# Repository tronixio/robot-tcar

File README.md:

# DRAFT - ROBOT - TCAR 4 Wheels.

## TCAR Features.

- 4 Wheels.
- 4 DC Motors.
- Power 2xCells 18650 Lithium Ion Rechargeable Batteries, with embedded charger.
- [4WD Motor Smart Car Chassis.](http://www.dagurobot.com/Robot-Chassis/HC021-P)

## TCAR All Schematics.

- [TODO - MCU Board PIC-16BIT.](https://github.com/tronixio/robot-tcar/blob/main/Kicad/mcu/extras/schematic.pdf)
- [DRAFT - Motors Board LP298.](https://github.com/tronixio/robot-tcar/blob/main/Kicad/motors/extras/schematic.pdf)

<!--
## TCAR Code.

- [PWM.](https://github.com/tronixio/robot-tbot/blob/main/Code/pwm/)

## TCAR MCU PIC 16Bit Top.

## TCAR MCU PIC 16Bit Bottom.

-->

## TCAR Motor Top.

## TCAR Motor Bottom.

!!! note

    - TODO : Work in progress, prototype was not good, hardware, PCB and code can be rework.
    - DRAFT : Prototype OK, last check schematic, PCB & code can be modify.

!!! example "DISCLAIMER"

    THIS CODE IS PROVIDED WITHOUT ANY WARRANTY OR GUARANTEES.
    USERS MAY USE THIS CODE FOR DEVELOPMENT AND EXAMPLE PURPOSES ONLY.
    AUTHORS ARE NOT RESPONSIBLE FOR ANY ERRORS, OMISSIONS, OR DAMAGES THAT COULD
    RESULT FROM USING THIS FIRMWARE IN WHOLE OR IN PART.

---

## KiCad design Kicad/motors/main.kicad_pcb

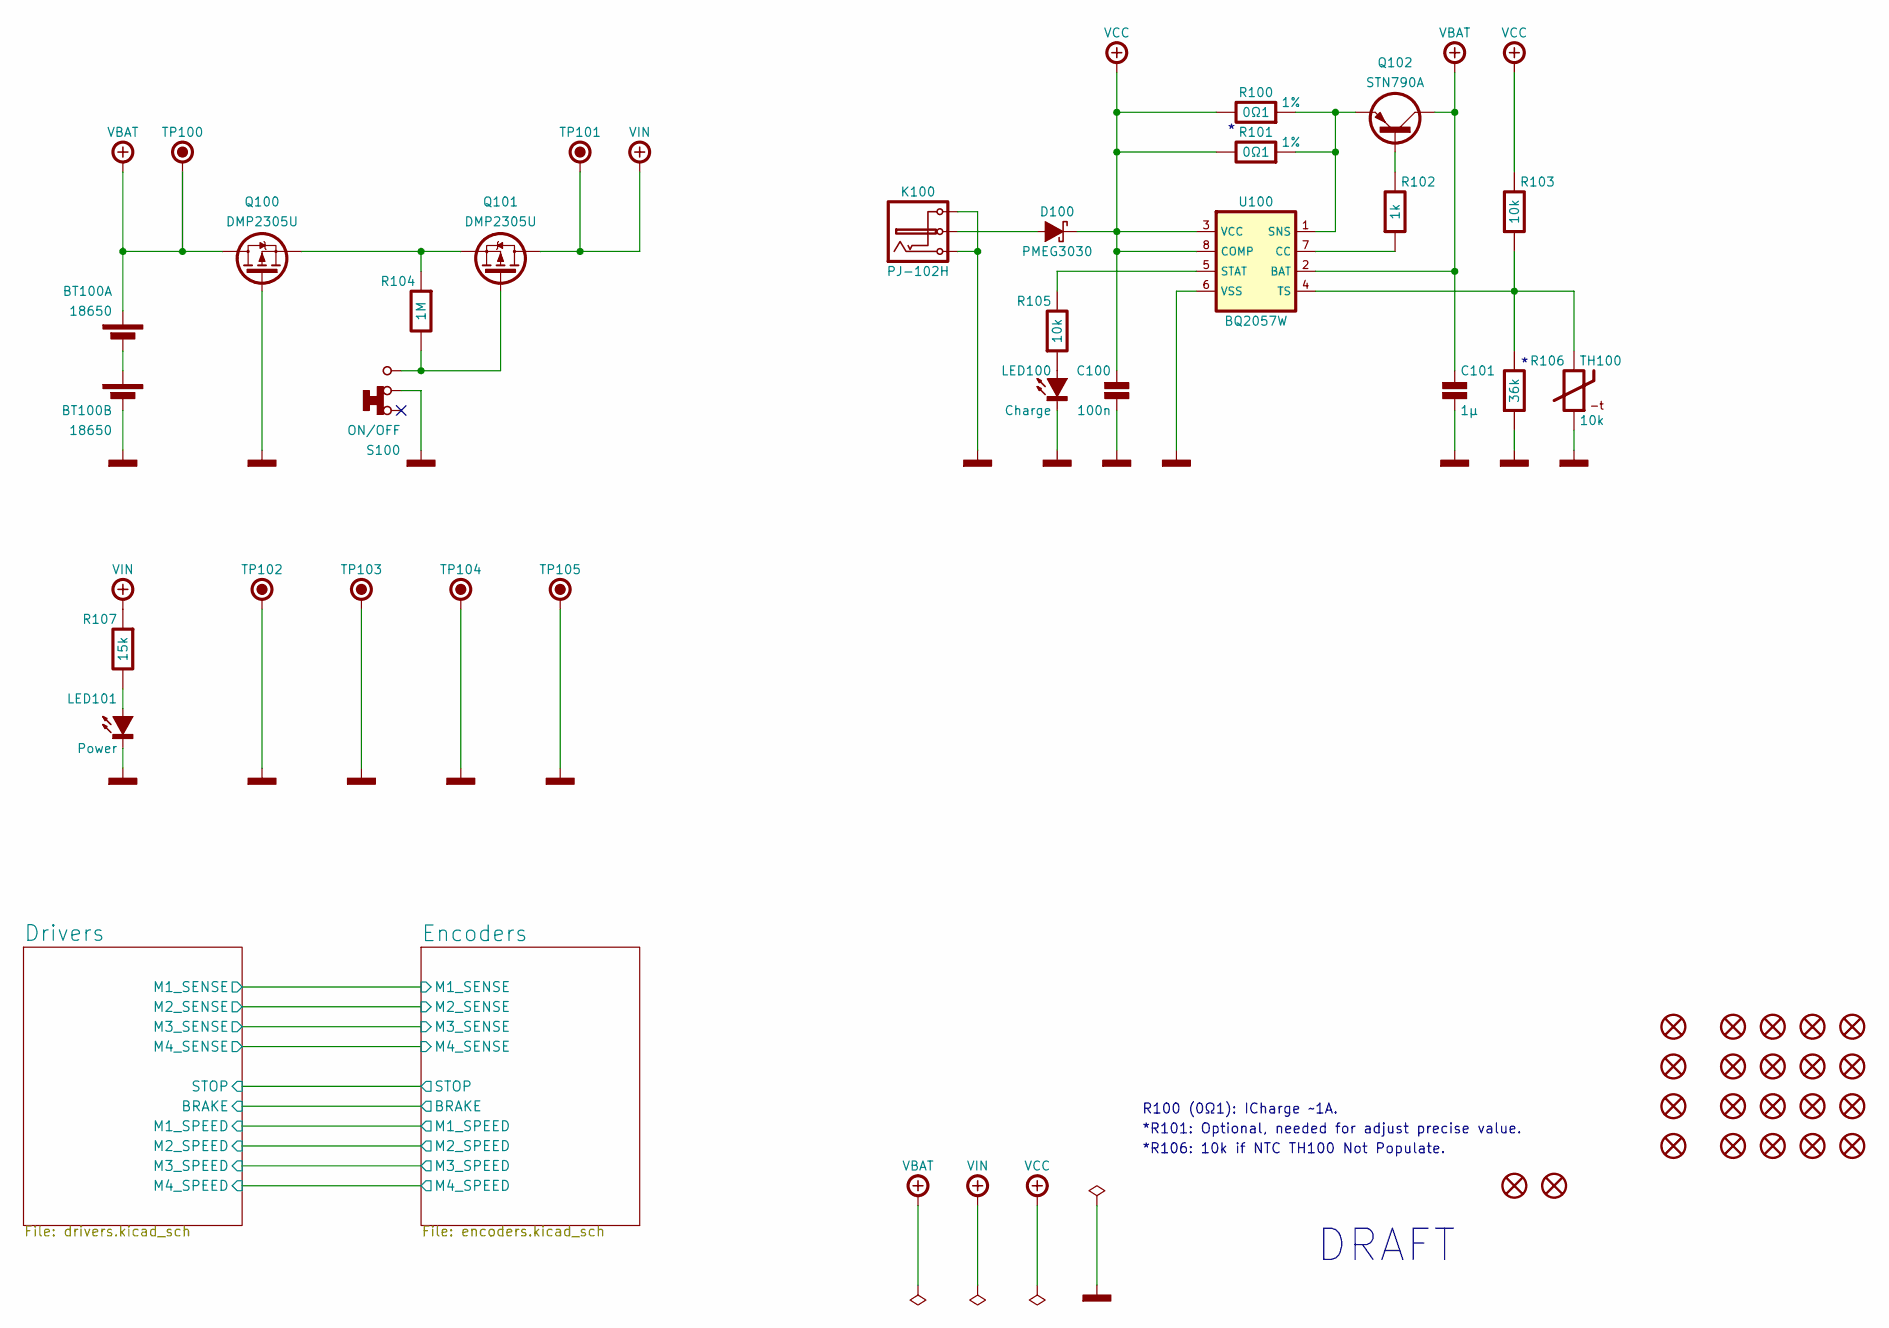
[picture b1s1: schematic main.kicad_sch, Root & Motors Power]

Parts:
BT100: 18650; KEYSTONE-1049; Mouser 534-1049
C100: 100n; CAPACITOR-SMD-1206; Voltage 50V; Tolerance 5%; Mouser 80-C1206C104J5R
C101: 1µ; CAPACITOR-SMD-1206; Voltage 16V; Tolerance 10%; Mouser 80-C1206C105K4R
D100: PMEG3030; SOD-128; Mouser 771-PMEG3030EP115
H101, H102, H103, H104, H105, H106, H107, H108, H109, H110, H111, H112, H113, H114, H115, H116: MOUNTING-HOLE-3MM-MASK
H117, H118, H119, H120: MOUNTING-HOLE-3.5MM
K100: PJ-102H; CUI-PJ-002AH-SMT-TR; Mouser 490-PJ-002AH-SMT-TR
LED100: Charge; LED-SMD-1206; Mouser 604-APT3216LSECKJ3RV
LED101: Power; LED-SMD-1206; Mouser 604-APT3216LSECKJ3RV
Q100, Q101: DMP2305U; SOT-23-3; Mouser 621-DMP2305U-7
Q102: STN790A; SOT-223-3; Mouser 511-STN790A
R100, R101: 0Ω1; RESISTOR-SMD-1210; Tolerance 1%; Mouser 660-SR732ETTER100F
R102: 1k; RESISTOR-SMD-1206; Tolerance 5%; Mouser 660-RK73B2BTTDD102J
R103, R105: 10k; RESISTOR-SMD-1206; Tolerance 5%; Mouser 660-RK73B2BTTDD103J
R104: 1M; RESISTOR-SMD-1206; Tolerance 5%; Mouser 660-RK73B2BTTDD105J
R106: 36k; RESISTOR-SMD-1206; Tolerance 5%; Mouser 660-RK73B2BTTDD363J
R107: 15k; RESISTOR-SMD-1206; Tolerance 5%; Mouser 660-RK73B2BTTDD153J
S100: ON/OFF; E-SWITCH-200USPXT1A1M6RE; Mouser 612-200USP1T1A1M6RE
TH100: 10k; THERMISTOR-SMD; Mouser 594-NTCLE213E3103FL
TP100, TP101, TP102, TP103, TP104, TP105: HARWIN-S1751; Mouser 855-S1751-46
U100: BQ2057W; SOIC-08; Mouser 595-BQ2057WSN
X101, X102: OSHW-5MM

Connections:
+VBAT: BT100.2 (+), C101.1, Q100.3 (D), Q102.2 (C), TP100.1, U100.2 (BAT)
+VCC: C100.1, D100.1 (C), R100.1, R101.1, R103.1, U100.3 (VCC), U100.8 (COMP)
+VIN: Q101.3 (D), R107.2, TP101.1; also elsewhere on the board
GND: BT100.3 (-), C100.2, C101.2, K100.2, K100.3, LED100.1 (C), LED101.1 (C), Q100.1 (G), R106.2, S100.2, TH100.2, TP102.1, TP103.1, TP104.1, TP105.1, U100.6 (VSS); also elsewhere on the board
unnamed: BT100.1 (-), BT100.4 (+)
unnamed: D100.2 (A), K100.1
unnamed: LED100.2 (A), R105.2
unnamed: LED101.2 (A), R107.1
unnamed: Q100.2 (S), Q101.2 (S), R104.2
unnamed: Q101.1 (G), R104.1, S100.3
unnamed: Q102.1 (B), R102.1
unnamed: Q102.3 (E), R100.2, R101.2, U100.1 (SNS)
unnamed: R102.2, U100.7 (CC)
unnamed: R105.1, U100.5 (STAT)
unnamed: R103.2, R106.1, TH100.1, U100.4 (TS)

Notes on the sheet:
DRAFT
*R101: Optional, needed for adjust precise value.
*R106: 10k if NTC TH100 Not Populate.
R100 (0Ω1): ICharge ~1A.

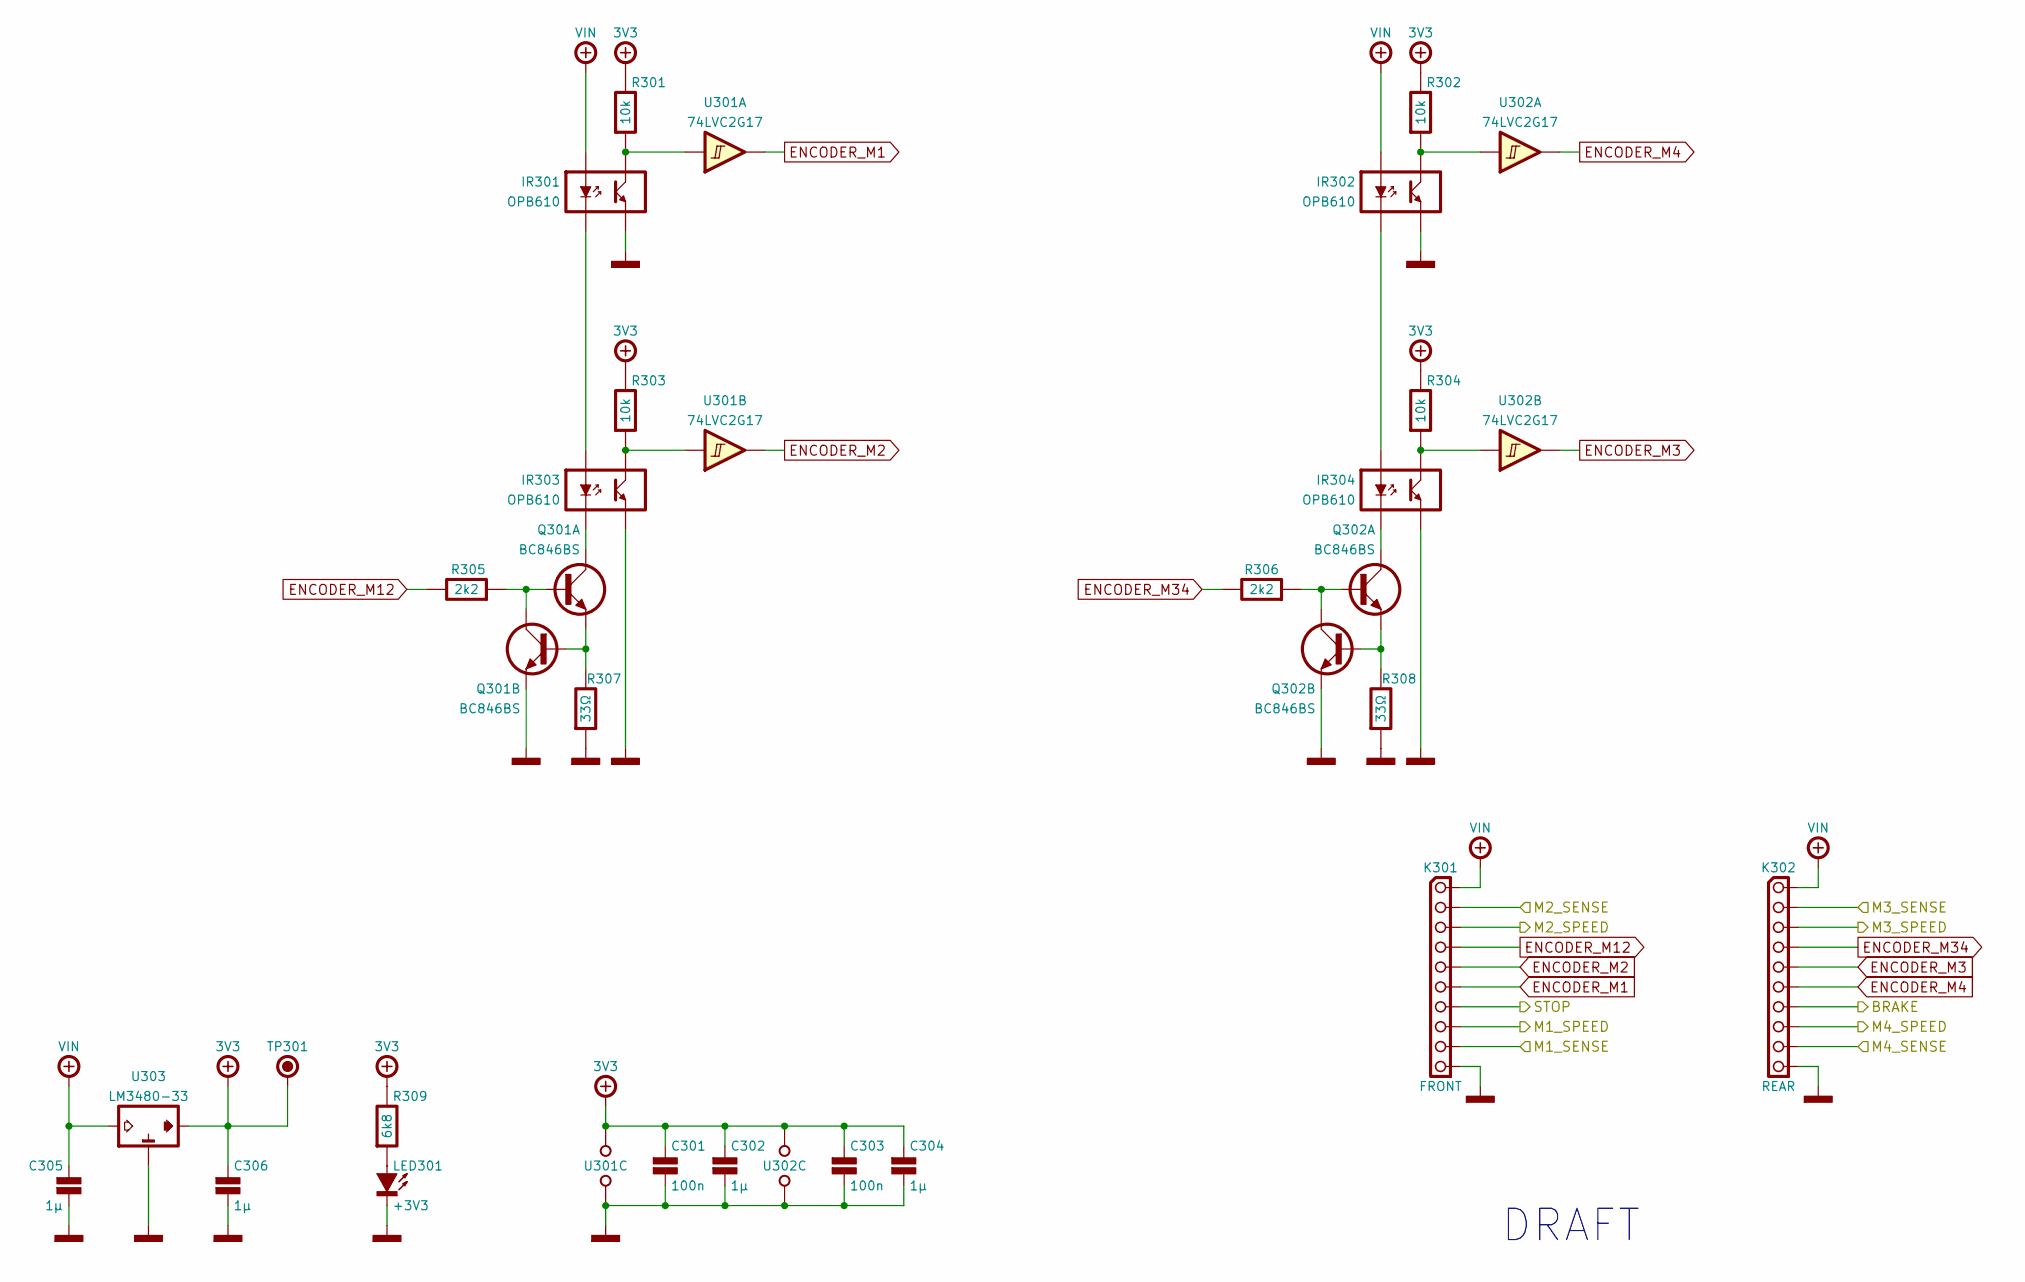
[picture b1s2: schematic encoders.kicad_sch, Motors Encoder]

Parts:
C301, C303: 100n; CAPACITOR-SMD-1206; Voltage 50V; Tolerance 5%; Mouser 80-C1206C104J5R
C302, C304, C305, C306: 1µ; CAPACITOR-SMD-1206; Voltage 16V; Tolerance 10%; Mouser 80-C1206C105K4R
IR301, IR302, IR303, IR304: OPB610; OPB-610; Mouser 828-OPB610
K301: FRONT; HARWIN-M20-782104x; Mouser 855-M20-782104
K302: REAR; HARWIN-M20-782104x; Mouser 855-M20-782104
LED301: +3V3; LED-SMD-1206; Mouser 604-APT3216LSECKJ3RV
Q301, Q302: BC846BS; SC-70-6; Mouser 771-BC846BS115
R301, R302, R303, R304: 10k; RESISTOR-SMD-1206; Tolerance 5%; Mouser 660-RK73B2BTTDD103J
R305, R306: 2k2; RESISTOR-SMD-1206; Tolerance 5%; Mouser 660-RK73B2BTTDD222J
R307, R308: 33Ω; RESISTOR-SMD-1206; Tolerance 5%; Mouser 660-RK73B2BTTDD330J
R309: 6k8; RESISTOR-SMD-1206; Tolerance 5%; Mouser 660-RK73B2BTTD682J
TP301: HARWIN-S1751; Mouser 855-S1751-46
U301, U302: 74LVC2G17; SOT-23-6; Mouser 595-SN74LVC2G17D
U303: LM3480-33; SOT-23-3; Mouser 926-LM3480IM33.3NOPB

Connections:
+3V3: C301.1, C302.1, C303.1, C304.1, C306.1, R301.1, R302.1, R303.1, R304.1, R309.1, TP301.1, U301.5 (VCC), U302.5 (VCC), U303.1 (VOUT); also elsewhere on the board
+VIN: C305.1, IR301.1 (ANODE), IR302.1 (ANODE), K301.1, K302.1, U303.2 (VIN); also elsewhere on the board
/Drivers/BRAKE: K302.7; also elsewhere on the board
/Drivers/M1_SENSE: K301.9; also elsewhere on the board
/Drivers/M1_SPEED: K301.8; also elsewhere on the board
/Drivers/M2_SENSE: K301.2; also elsewhere on the board
/Drivers/M2_SPEED: K301.3; also elsewhere on the board
/Drivers/M3_SENSE: K302.2; also elsewhere on the board
/Drivers/M3_SPEED: K302.3; also elsewhere on the board
/Drivers/M4_SENSE: K302.9; also elsewhere on the board
/Drivers/M4_SPEED: K302.8; also elsewhere on the board
/Drivers/STOP: K301.7; also elsewhere on the board
ENCODER_M1: K301.6, U301.6 (1Y)
ENCODER_M2: K301.5, U301.4 (2Y)
ENCODER_M3: K302.5, U302.4 (2Y)
ENCODER_M4: K302.6, U302.6 (1Y)
ENCODER_M12: K301.4, R305.1
ENCODER_M34: K302.4, R306.1
GND: C301.2, C302.2, C303.2, C304.2, C305.2, C306.2, IR301.4 (EMITTER), IR302.4 (EMITTER), IR303.4 (EMITTER), IR304.4 (EMITTER), K301.10, K302.10, LED301.1 (C), Q301.4 (E), Q302.4 (E), R307.2, R308.2, U301.2 (GND), U302.2 (GND), U303.3 (GND); also elsewhere on the board
unnamed: IR301.2 (CATHODE), IR303.1 (ANODE)
unnamed: IR301.3 (COLLECTOR), R301.2, U301.1 (1A)
unnamed: IR302.2 (CATHODE), IR304.1 (ANODE)
unnamed: IR302.3 (COLLECTOR), R302.2, U302.1 (1A)
unnamed: IR303.2 (CATHODE), Q301.6 (C)
unnamed: IR303.3 (COLLECTOR), R303.2, U301.3 (2A)
unnamed: IR304.2 (CATHODE), Q302.6 (C)
unnamed: IR304.3 (COLLECTOR), R304.2, U302.3 (2A)
unnamed: LED301.2 (A), R309.2
unnamed: Q301.2 (B), Q301.3 (C), R305.2
unnamed: Q301.1 (E), Q301.5 (B), R307.1
unnamed: Q302.2 (B), Q302.3 (C), R306.2
unnamed: Q302.1 (E), Q302.5 (B), R308.1

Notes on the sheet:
DRAFT

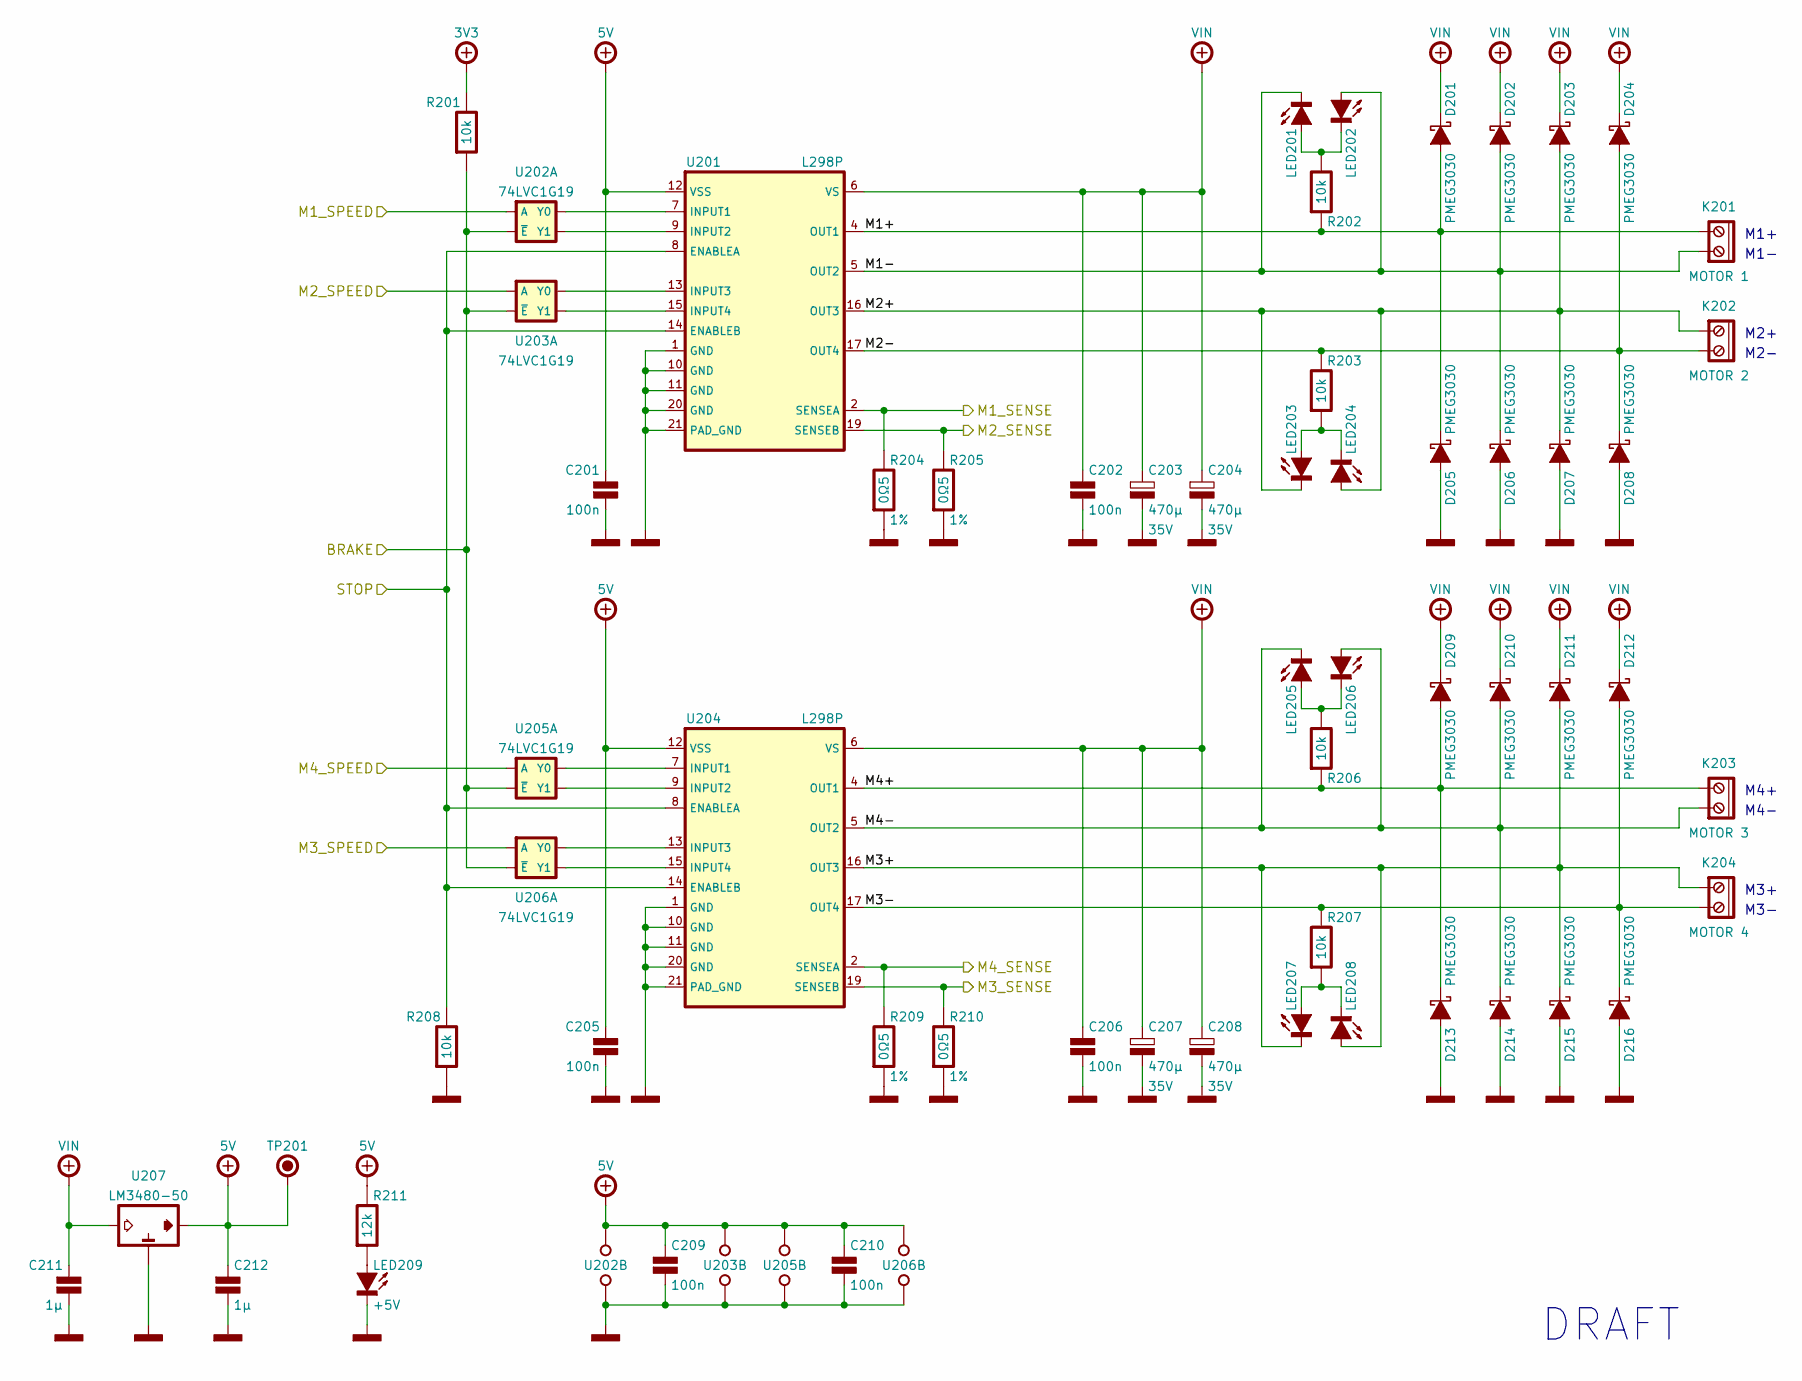
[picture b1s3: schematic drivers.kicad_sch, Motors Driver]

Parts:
C201, C202, C205, C206, C209, C210: 100n; CAPACITOR-SMD-1206; Voltage 50V; Tolerance 5%; Mouser 80-C1206C104J5R
C203, C204, C207, C208: 470µ; CAPACITOR-ELECTROLYTIC-RADIAL-100-160-050-WURTH; Tolerance 20%; Voltage 35V; Mouser 710-860010575013
C211, C212: 1µ; CAPACITOR-SMD-1206; Voltage 16V; Tolerance 10%; Mouser 80-C1206C105K4R
D201, D202, D203, D204, D205, D206, D207, D208, D209, D210, D211, D212, D213, D214, D215, D216: PMEG3030; SOD-128; Mouser 771-PMEG3030EP115
K201: MOTOR 1; CUI-TB006-508-02BE; Mouser 490-TB006-508-02BE
K202: MOTOR 2; CUI-TB006-508-02BE; Mouser 490-TB006-508-02BE
K203: MOTOR 3; CUI-TB006-508-02BE; Mouser 490-TB006-508-02BE
K204: MOTOR 4; CUI-TB006-508-02BE; Mouser 490-TB006-508-02BE
LED201, LED202, LED203, LED204, LED205, LED206, LED207, LED208: RED; LED-SMD-1206; Mouser 604-APT3216LSECKJ3RV
LED209: +5V; LED-SMD-1206; Mouser 604-APT3216LSECKJ3RV
R201, R202, R203, R206, R207, R208: 10k; RESISTOR-SMD-1206; Tolerance 5%; Mouser 660-RK73B2BTTDD103J
R204, R205, R209, R210: 0Ω5; RESISTOR-SMD-1210; Tolerance 1%; Mouser 660-SR732ETTDR499F
R211: 12k; RESISTOR-SMD-1206; Tolerance 5%; Mouser 660-RK73B2BTTD123J
TP201: HARWIN-S1751; Mouser 855-S1751-46
U201, U204: L298P; SOPOWER-20; Mouser 511-L298P-TR
U202, U203, U205, U206: 74LVC1G19; SOT-23-6; Mouser 595-SN74LVC1G19D
U207: LM3480-50; SOT-23-3; Mouser 926-LM3480IM35.0NOPB

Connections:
+3V3: R201.1; also elsewhere on the board
+5V: C201.1, C205.1, C209.1, C210.1, C212.1, R211.1, TP201.1, U201.12 (VSS), U202.5 (VCC), U203.5 (VCC), U204.12 (VSS), U205.5 (VCC), U206.5 (VCC), U207.1 (VOUT)
+VIN: C202.1, C203.1, C204.1, C206.1, C207.1, C208.1, C211.1, D201.1 (C), D202.1 (C), D203.1 (C), D204.1 (C), D209.1 (C), D210.1 (C), D211.1 (C), D212.1 (C), U201.6 (VS), U204.6 (VS), U207.2 (VIN); also elsewhere on the board
/Drivers/BRAKE: R201.2, U202.3 (~E), U203.3 (~E), U205.3 (~E), U206.3 (~E); also elsewhere on the board
/Drivers/M1+: D201.2 (A), D205.1 (C), K201.2, R202.2, U201.4 (OUT1)
/Drivers/M1-: D202.2 (A), D206.1 (C), K201.1, LED201.1 (C), LED202.2 (A), U201.5 (OUT2)
/Drivers/M1_SENSE: R204.1, U201.2 (SENSEA); also elsewhere on the board
/Drivers/M1_SPEED: U202.1 (A); also elsewhere on the board
/Drivers/M2+: D203.2 (A), D207.1 (C), K202.1, LED203.1 (C), LED204.2 (A), U201.16 (OUT3)
/Drivers/M2-: D204.2 (A), D208.1 (C), K202.2, R203.1, U201.17 (OUT4)
/Drivers/M2_SENSE: R205.1, U201.19 (SENSEB); also elsewhere on the board
/Drivers/M2_SPEED: U203.1 (A); also elsewhere on the board
/Drivers/M3+: D211.2 (A), D215.1 (C), K204.1, LED207.1 (C), LED208.2 (A), U204.16 (OUT3)
/Drivers/M3-: D212.2 (A), D216.1 (C), K204.2, R207.1, U204.17 (OUT4)
/Drivers/M3_SENSE: R210.1, U204.19 (SENSEB); also elsewhere on the board
/Drivers/M3_SPEED: U206.1 (A); also elsewhere on the board
/Drivers/M4+: D209.2 (A), D213.1 (C), K203.2, R206.2, U204.4 (OUT1)
/Drivers/M4-: D210.2 (A), D214.1 (C), K203.1, LED205.1 (C), LED206.2 (A), U204.5 (OUT2)
/Drivers/M4_SENSE: R209.1, U204.2 (SENSEA); also elsewhere on the board
/Drivers/M4_SPEED: U205.1 (A); also elsewhere on the board
/Drivers/STOP: R208.1, U201.8 (ENABLEA), U201.14 (ENABLEB), U204.8 (ENABLEA), U204.14 (ENABLEB); also elsewhere on the board
GND: C201.2, C202.2, C203.2, C204.2, C205.2, C206.2, C207.2, C208.2, C209.2, C210.2, C211.2, C212.2, D205.2 (A), D206.2 (A), D207.2 (A), D208.2 (A), D213.2 (A), D214.2 (A), D215.2 (A), D216.2 (A), LED209.1 (C), R204.2, R205.2, R208.2, R209.2, R210.2, U201.1 (GND), U201.10 (GND), U201.11 (GND), U201.20 (GND), U201.21 (PAD_GND), U202.2 (GND), U203.2 (GND), U204.1 (GND), U204.10 (GND), U204.11 (GND), U204.20 (GND), U204.21 (PAD_GND), U205.2 (GND), U206.2 (GND), U207.3 (GND); also elsewhere on the board
unnamed: LED201.2 (A), LED202.1 (C), R202.1
unnamed: LED203.2 (A), LED204.1 (C), R203.2
unnamed: LED205.2 (A), LED206.1 (C), R206.1
unnamed: LED207.2 (A), LED208.1 (C), R207.2
unnamed: LED209.2 (A), R211.2
unnamed: U201.7 (INPUT1), U202.6 (Y0)
unnamed: U201.9 (INPUT2), U202.4 (Y1)
unnamed: U201.13 (INPUT3), U203.6 (Y0)
unnamed: U201.15 (INPUT4), U203.4 (Y1)
unnamed: U204.7 (INPUT1), U205.6 (Y0)
unnamed: U204.9 (INPUT2), U205.4 (Y1)
unnamed: U204.13 (INPUT3), U206.6 (Y0)
unnamed: U204.15 (INPUT4), U206.4 (Y1)

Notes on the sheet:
M3-
M1+
M2+
M4-
M2-
DRAFT
M3+
M4+
M1-

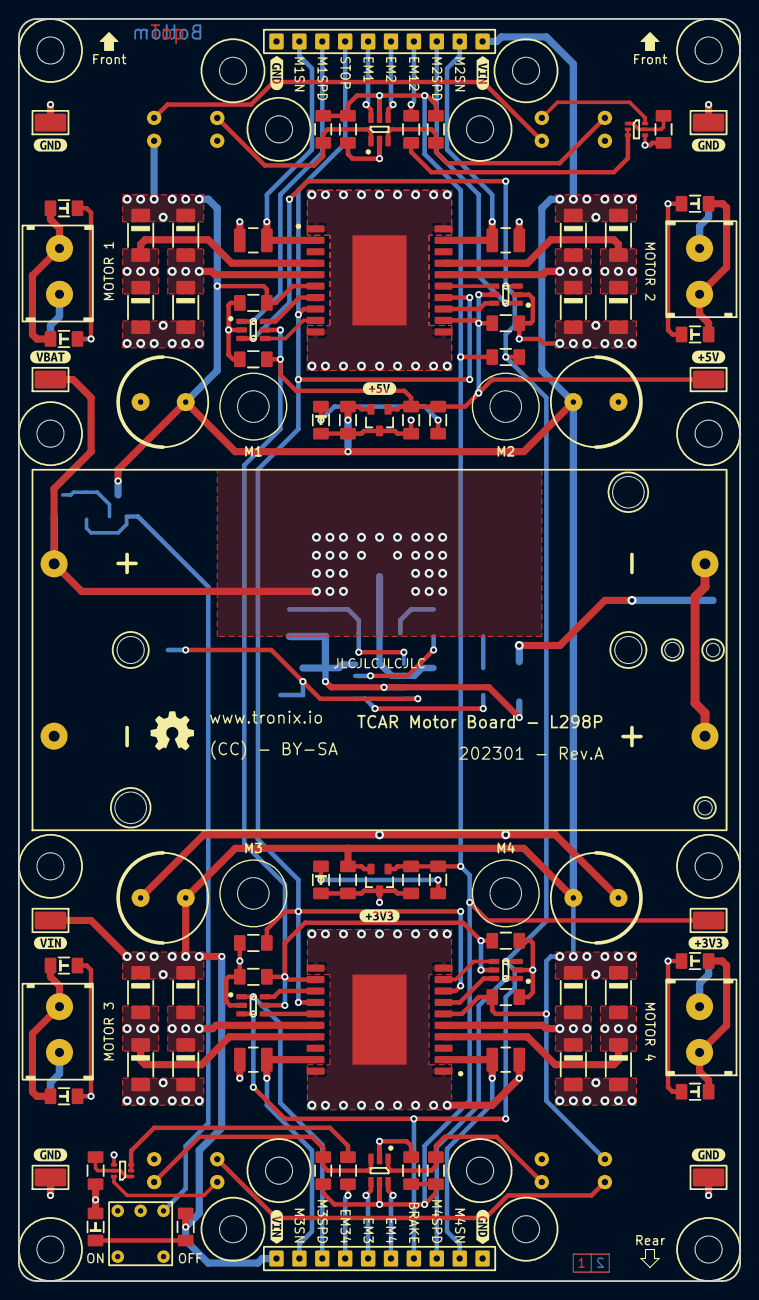
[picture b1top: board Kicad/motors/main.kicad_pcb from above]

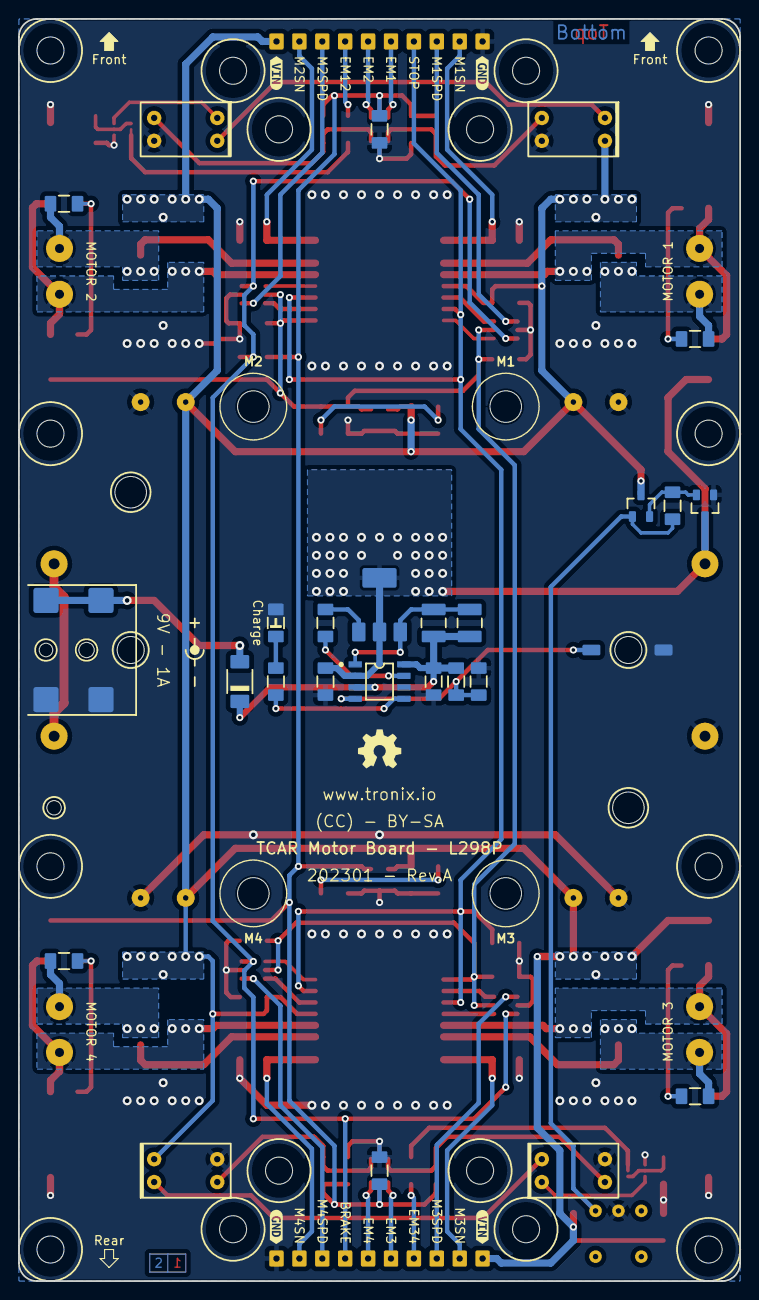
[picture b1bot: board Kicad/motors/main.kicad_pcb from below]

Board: 2 copper layers, 80.0 x 140.0 mm, 155 parts (32 on the bottom side), 67 nets.

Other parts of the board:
kibuzzard-64482FBD: G***; kibuzzard-64482FBD
kibuzzard-64482FE5: G***; kibuzzard-64482FE5
kibuzzard-628974BE, kibuzzard-628974BE#2: G***; kibuzzard-628974BE
kibuzzard-628977DB: G***; kibuzzard-628977DB
kibuzzard-628977F0: G***; kibuzzard-628977F0
kibuzzard-6289753B, kibuzzard-6289753B#2: G***; kibuzzard-6289753B
kibuzzard-6289769F, kibuzzard-6289769F#2: G***; kibuzzard-6289769F
kibuzzard-6289784D: G***; kibuzzard-6289784D
kibuzzard-6289786A: G***; kibuzzard-6289786A
kibuzzard-62897416, kibuzzard-62897416#2: G***; kibuzzard-62897416
kibuzzard-62897505, kibuzzard-62897505#2: G***; kibuzzard-62897505
kibuzzard-62897802: G***; kibuzzard-62897802
kibuzzard-62897881: G***; kibuzzard-62897881

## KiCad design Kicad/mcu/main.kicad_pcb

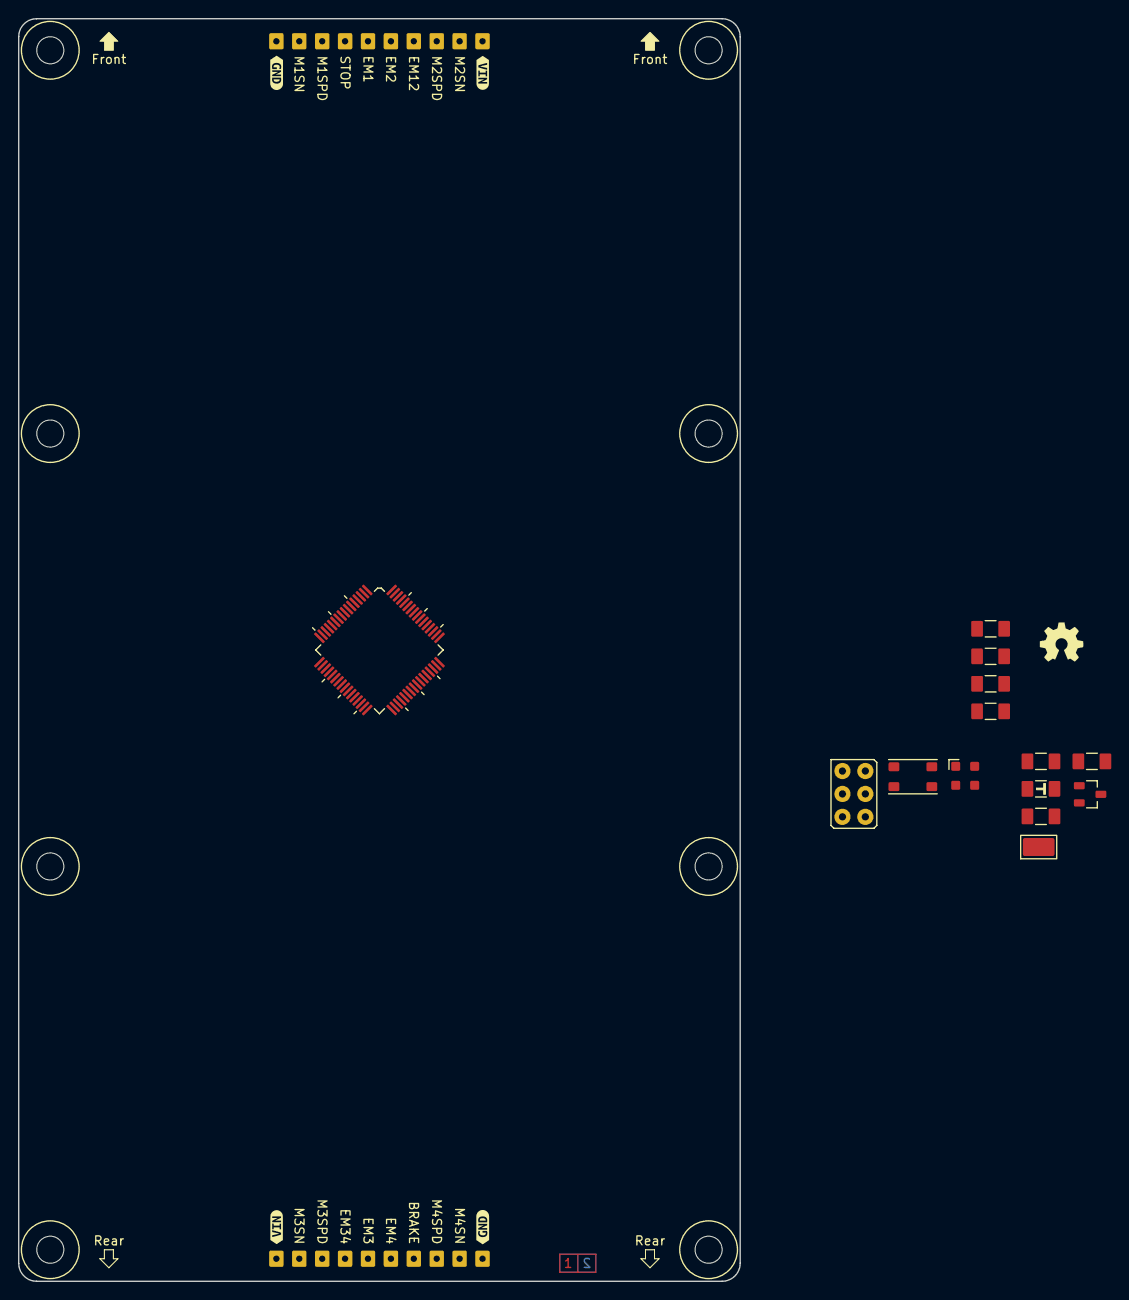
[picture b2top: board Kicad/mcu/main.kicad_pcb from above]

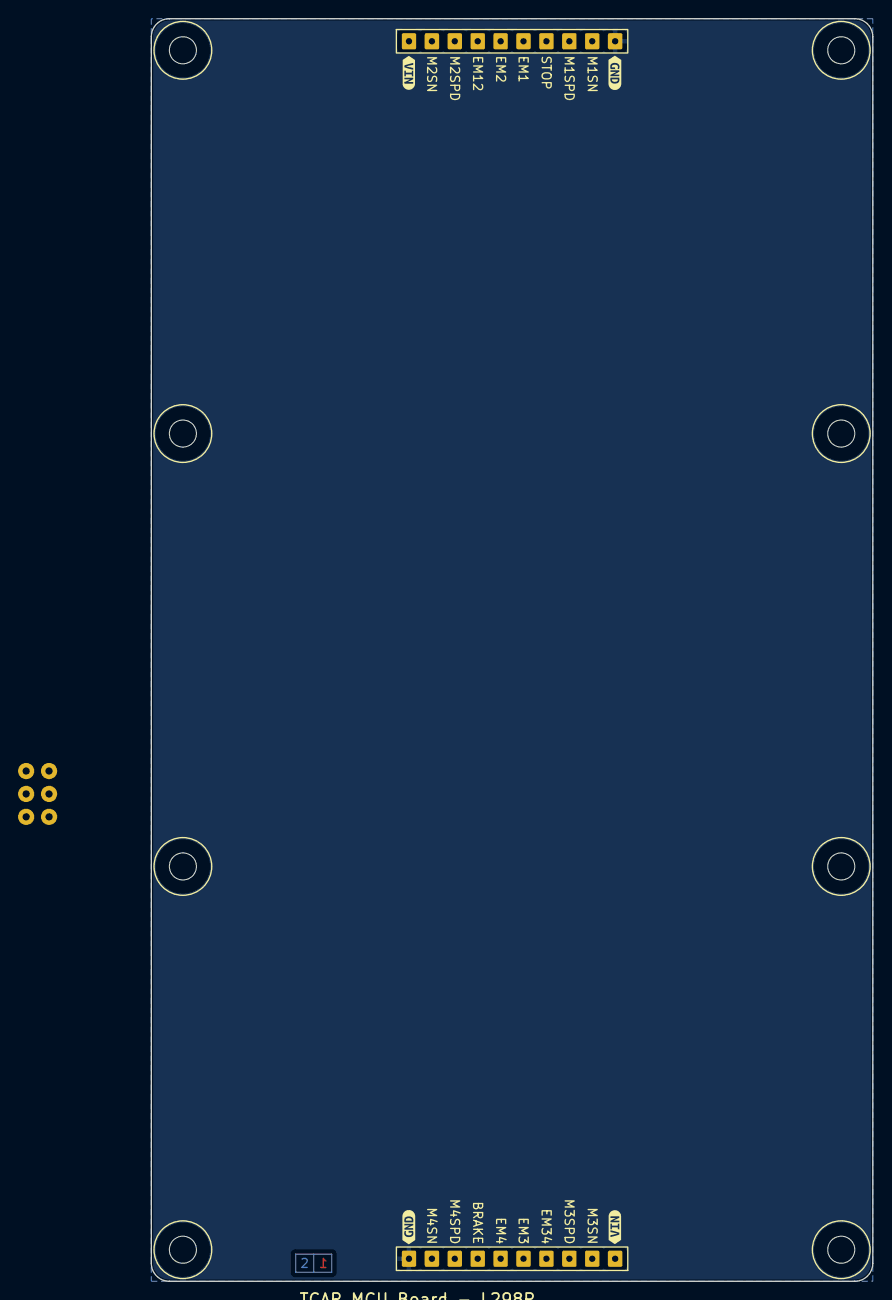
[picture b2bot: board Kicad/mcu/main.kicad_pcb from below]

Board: 2 copper layers, 80.0 x 140.0 mm, 34 parts (7 on the bottom side), 5 nets, no tracks yet.

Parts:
C101, C102: 1µ; CAPACITOR-SMD-1206
C201, C202: 100n; CAPACITOR-SMD-1206
H101, H102, H103, H104, H105, H106, H107, H108: MOUNTING-HOLE-MASK-3MM; MOUNTING-HOLE-3MM-MASK
IC101: LM3480-33; SOT-23-3
IC201: MICROCHIP-PIC24FJ64GA106-TQFP; TQFP-64
K201: ICSP; HARWIN-M20-998034x
K301: Front; HARWIN-M20-782104x
K302: Rear; HARWIN-M20-782104x
LED101: Power; LED-SMD-1206
MEMS201: MICROCHIP-DSC1001C-245760-CDFN; CDFN-3225
R101: 6K8; RESISTOR-SMD-1206
R201: 10K; RESISTOR-SMD-1206
R202: 1K; RESISTOR-SMD-1206
S201: Reset; ALPS-SKRPAC
TP101: HARWIN-S1751
X101, X102: SYMBOL-MISC; OSHW-5MM
kibuzzard-64205CDF, kibuzzard-64205CDF#2, kibuzzard-64205CDF#3, kibuzzard-64205CDF#4: G***; kibuzzard-64205CDF
kibuzzard-628974BE, kibuzzard-628974BE#2, kibuzzard-628974BE#3, kibuzzard-628974BE#4: G***; kibuzzard-628974BE

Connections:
+3V3: C102.1, C202.1, K201.2 (VDD), R101.1, TP101.1
GND: C101.2, C102.2, C201.2, C202.2, IC101.3 (GND), K301.1, K302.1, LED101.1 (C), S201.1, S201.2
unnamed: C201.1, R201.1, R202.2, S201.3, S201.4
unnamed: LED101.2 (A), R101.2
VIN: C101.1, K301.10, K302.10

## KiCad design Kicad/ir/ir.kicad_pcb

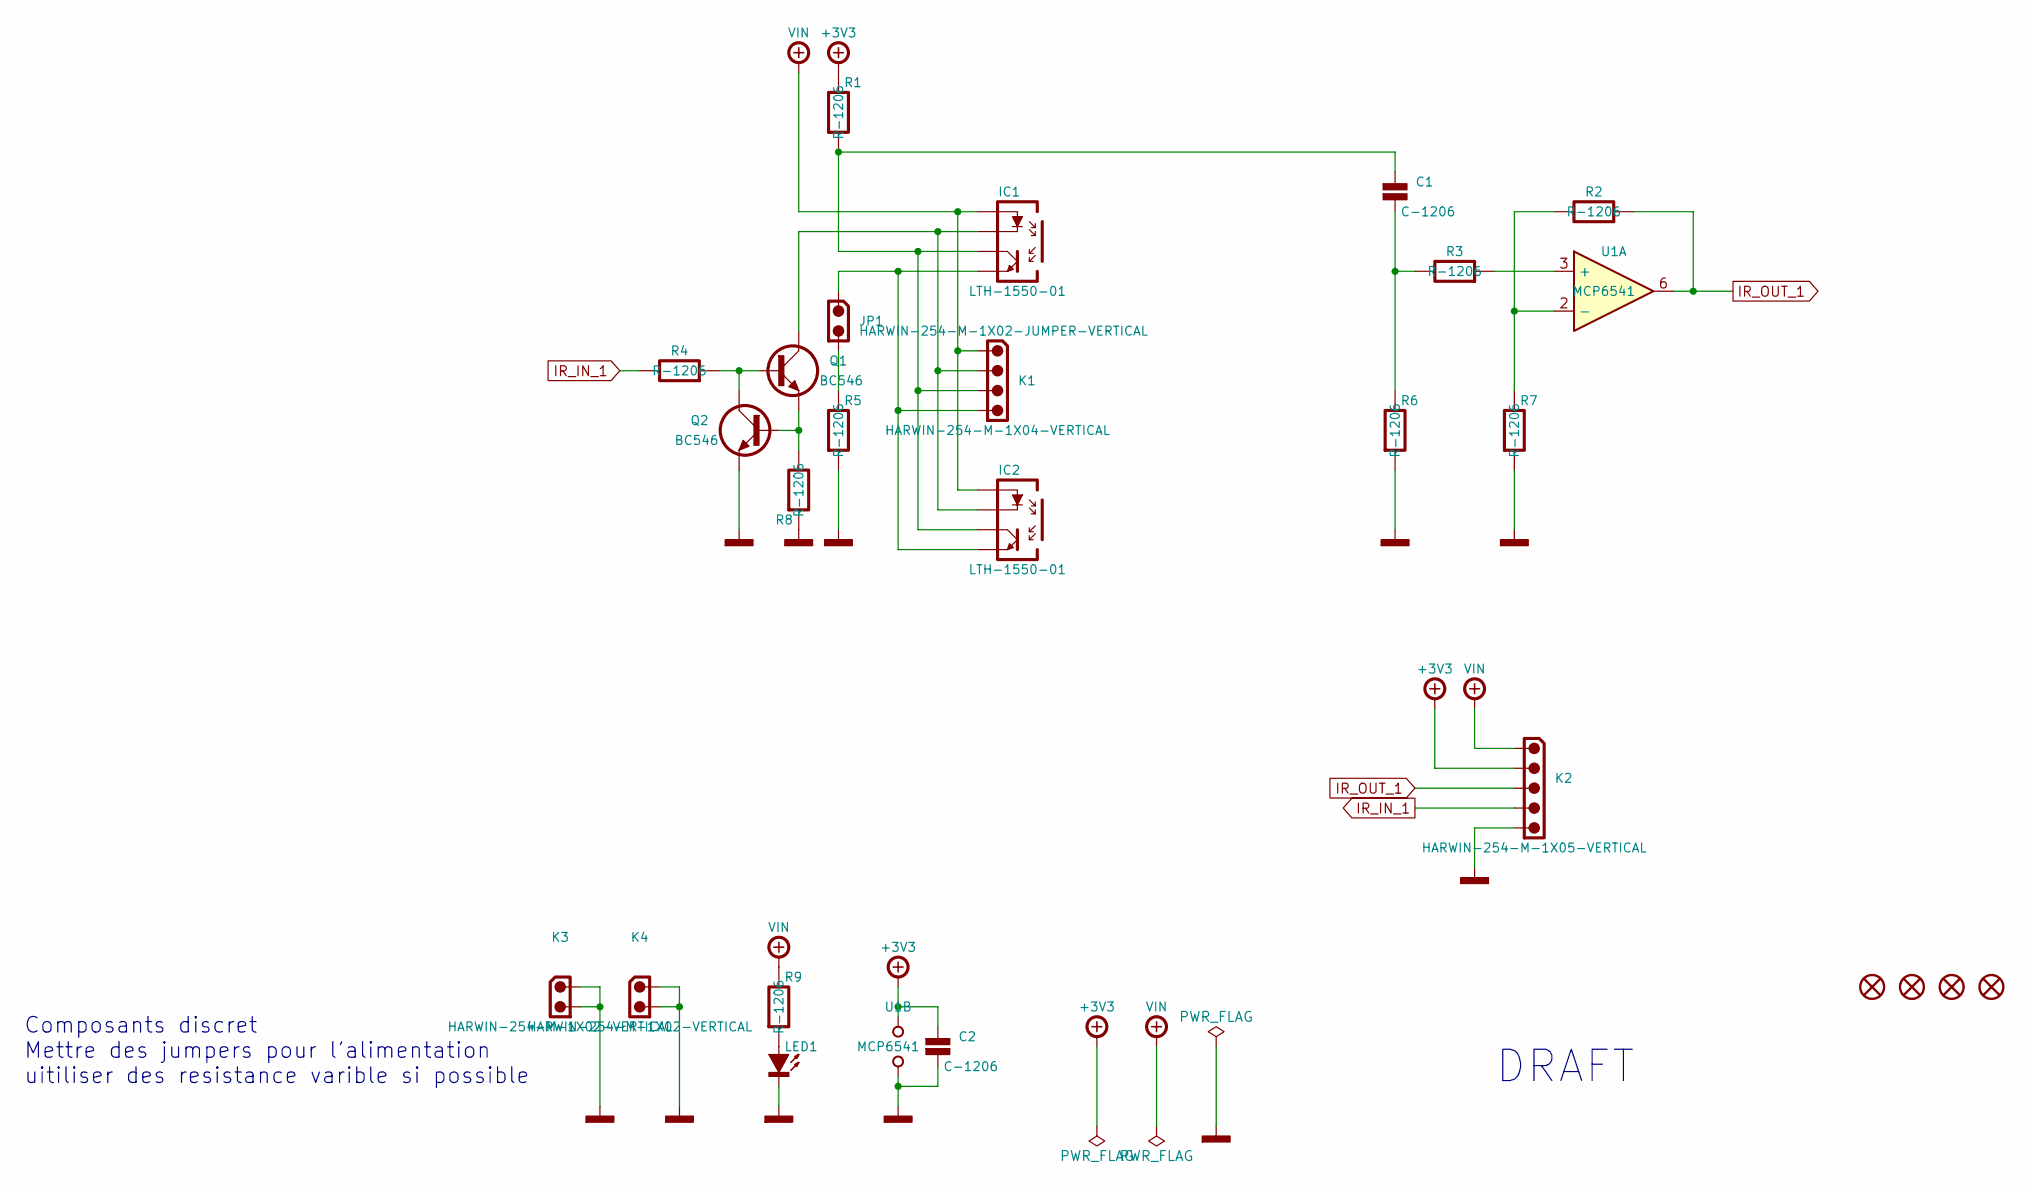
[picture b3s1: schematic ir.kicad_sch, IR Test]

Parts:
C1, C2: C-1206
H1, H2, H3, H4: MOUNTING-HOLE-MASK-3MM; M3-MASK
IC1, IC2: Mouser 859-LTH-1550-01
JP1: HARWIN-254-M-1X02-JUMPER-VERTICAL; HARWIN-M20-999024x; Mouser 855-M20-999024
K1: HARWIN-254-M-1X04-VERTICAL; HARWIN-M20-999044x; Mouser 855-M20-999044
K2: HARWIN-254-M-1X05-VERTICAL; HARWIN-M20-999054x; Mouser 855-M20-999054
K3, K4: HARWIN-254-M-1X02-VERTICAL; HARWIN-M20-999024x; Mouser 55-M20-9990245
LED1: Mouser 604-APT3216LSECKJ3RV
Q1: Mouser 512-BC546ABU
Q2: ONSEMI-BC546-TO92; TO-92-INLINE; Mouser 512-BC546ABU
R1, R2, R3, R4, R5, R6, R7, R8, R9: R-1206
U1: Mouser 579-MCP6541-I/P

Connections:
+3V3: C2.1, K2.2, R1.1, U1.7 (VDD)
GND: C2.2, K2.5, K3.1, K3.2, K4.1, K4.2, LED1.1 (K), Q2.3 (E), R5.2, R6.2, R7.2, R8.2, U1.4 (GND)
IR_IN_1: K2.4, R4.1
IR_OUT_1: K2.3, R2.2, U1.6
unnamed: C1.1, IC1.3 (COLLECTOR), IC2.3 (COLLECTOR), K1.3, R1.2
unnamed: C1.2, R3.1, R6.1
unnamed: IC1.2 (CATHODE), IC2.2 (CATHODE), K1.2, Q1.1 (C)
unnamed: IC1.4 (EMITTER), IC2.4 (EMITTER), JP1.1, K1.4
unnamed: JP1.2, R5.1
unnamed: LED1.2 (A), R9.2
unnamed: Q1.2 (B), Q2.1 (C), R4.2
unnamed: Q1.3 (E), Q2.2 (B), R8.1
unnamed: R2.1, R7.1, U1.2 (-)
unnamed: R3.2, U1.3 (+)
VIN: IC1.1 (ANODE), IC2.1 (ANODE), K1.1, K2.1, R9.1

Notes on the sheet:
DRAFT
Composants discret Mettre des jumpers pour l'alimentation uitiliser des resistance varible si possible
